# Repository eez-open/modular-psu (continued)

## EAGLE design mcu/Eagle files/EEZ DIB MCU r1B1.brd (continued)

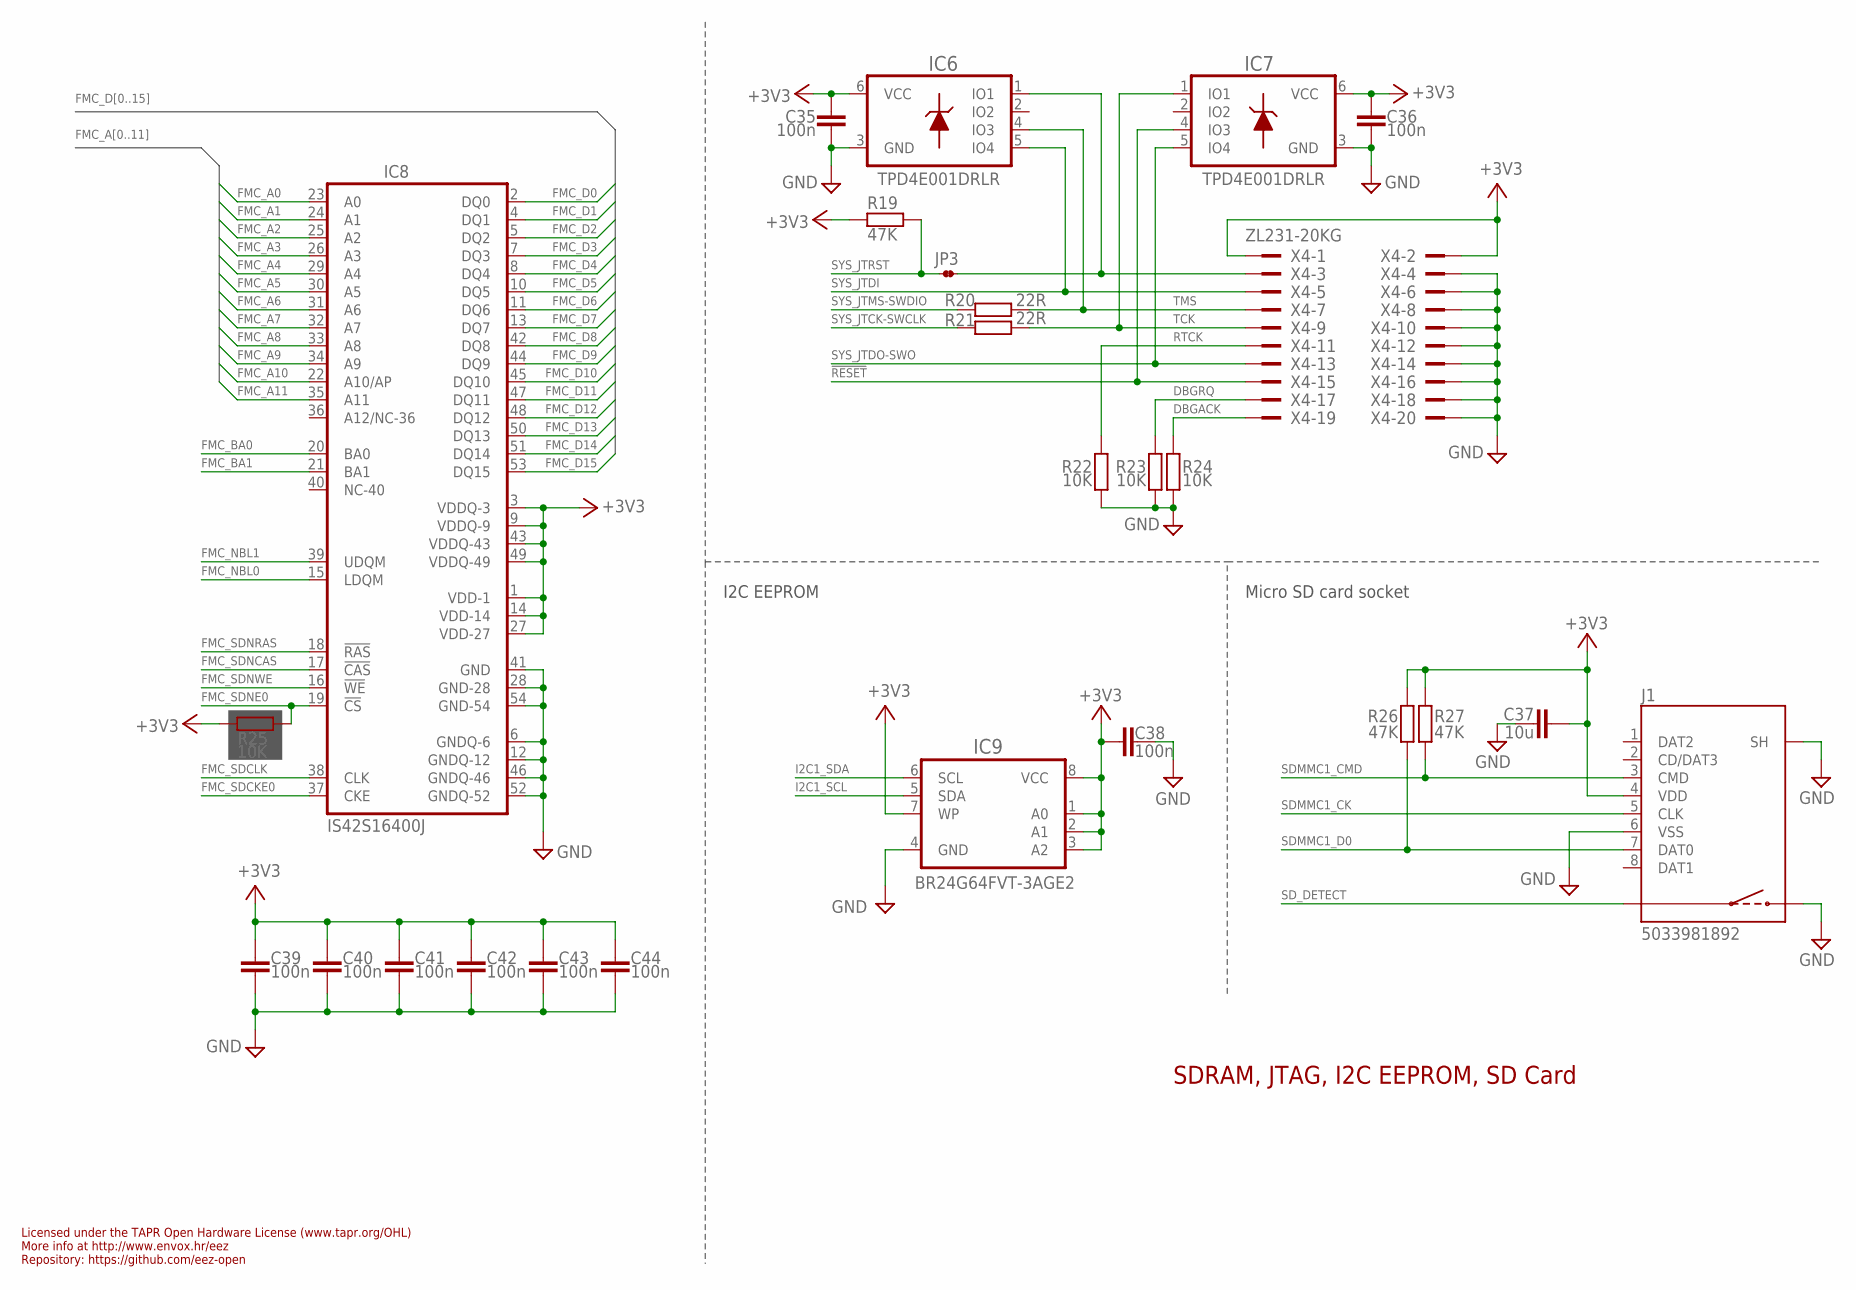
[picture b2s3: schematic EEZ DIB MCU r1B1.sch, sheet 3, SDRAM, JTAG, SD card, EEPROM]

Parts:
C35, C36, C38, C39, C40, C41, C42, C43, C44: 100n; C0603
C37: 10u; C1210
IC6, IC7: TPD4E001DRLR; DRL6
IC8: IS42S16400J; TSOPII-54
IC9: BR24G64FVT-3AGE2; PW8_TSSOP8
J1: 5033981892
JP3: JP2-NOCUT
R19, R26, R27: 47K; R0805
R20, R21: 22R; R0805
R22, R23, R24, R25: 10K; R0805
X4: ZL231-20KG; ML20L

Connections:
!RESET: IC7.4 (IO3), X4.15; also elsewhere on the board
+3V3: C35.1, C36.1, C37.1, C38.2, C39.1, C40.1, C41.1, C42.1, C43.1, C44.1, IC6.6 (VCC), IC7.6 (VCC), IC8.1 (VDD-1), IC8.3 (VDDQ-3), IC8.9 (VDDQ-9), IC8.14 (VDD-14), IC8.27 (VDD-27), IC8.43 (VDDQ-43), IC8.49 (VDDQ-49), IC9.1 (A0), IC9.2 (A1), IC9.3 (A2), IC9.7 (WP), IC9.8 (VCC), J1.4 (VDD), R19.1, R25.1, R26.1, R27.1, X4.1, X4.2; also elsewhere on the board
DBGACK: R24.1, X4.19
DBGRQ: R23.1, X4.17
FMC_A0: IC8.23 (A0); also elsewhere on the board
FMC_A1: IC8.24 (A1); also elsewhere on the board
FMC_A2: IC8.25 (A2); also elsewhere on the board
FMC_A3: IC8.26 (A3); also elsewhere on the board
FMC_A4: IC8.29 (A4); also elsewhere on the board
FMC_A5: IC8.30 (A5); also elsewhere on the board
FMC_A6: IC8.31 (A6); also elsewhere on the board
FMC_A7: IC8.32 (A7); also elsewhere on the board
FMC_A8: IC8.33 (A8); also elsewhere on the board
FMC_A9: IC8.34 (A9); also elsewhere on the board
FMC_A10: IC8.22 (A10/AP); also elsewhere on the board
FMC_A11: IC8.35 (A11); also elsewhere on the board
FMC_BA0: IC8.20 (BA0); also elsewhere on the board
FMC_BA1: IC8.21 (BA1); also elsewhere on the board
FMC_D0: IC8.2 (DQ0); also elsewhere on the board
FMC_D1: IC8.4 (DQ1); also elsewhere on the board
FMC_D2: IC8.5 (DQ2); also elsewhere on the board
FMC_D3: IC8.7 (DQ3); also elsewhere on the board
FMC_D4: IC8.8 (DQ4); also elsewhere on the board
FMC_D5: IC8.10 (DQ5); also elsewhere on the board
FMC_D6: IC8.11 (DQ6); also elsewhere on the board
FMC_D7: IC8.13 (DQ7); also elsewhere on the board
FMC_D8: IC8.42 (DQ8); also elsewhere on the board
FMC_D9: IC8.44 (DQ9); also elsewhere on the board
FMC_D10: IC8.45 (DQ10); also elsewhere on the board
FMC_D11: IC8.47 (DQ11); also elsewhere on the board
FMC_D12: IC8.48 (DQ12); also elsewhere on the board
FMC_D13: IC8.50 (DQ13); also elsewhere on the board
FMC_D14: IC8.51 (DQ14); also elsewhere on the board
FMC_D15: IC8.53 (DQ15); also elsewhere on the board
FMC_NBL0: IC8.15 (LDQM); also elsewhere on the board
FMC_NBL1: IC8.39 (UDQM); also elsewhere on the board
FMC_SDCKE0: IC8.37 (CKE); also elsewhere on the board
FMC_SDCLK: IC8.38 (CLK); also elsewhere on the board
FMC_SDNCAS: IC8.17 (!CAS); also elsewhere on the board
FMC_SDNE0: IC8.19 (!CS), R25.2; also elsewhere on the board
FMC_SDNRAS: IC8.18 (!RAS); also elsewhere on the board
FMC_SDNWE: IC8.16 (!WE); also elsewhere on the board
GND: C35.2, C36.2, C37.2, C38.1, C39.2, C40.2, C41.2, C42.2, C43.2, C44.2, IC6.3 (GND), IC7.3 (GND), IC8.6 (GNDQ-6), IC8.12 (GNDQ-12), IC8.28 (GND-28), IC8.41 (GND), IC8.46 (GNDQ-46), IC8.52 (GNDQ-52), IC8.54 (GND-54), IC9.4 (GND), J1.6 (VSS), J1.S (SH), J1.SW2, R22.2, R23.2, R24.2, X4.4, X4.6, X4.8, X4.10, X4.12, X4.14, X4.16, X4.18, X4.20; also elsewhere on the board
I2C1_SCL: IC9.5 (SDA); also elsewhere on the board
I2C1_SDA: IC9.6 (SCL); also elsewhere on the board
RTCK: R22.1, X4.11
SDMMC1_CK: J1.5 (CLK); also elsewhere on the board
SDMMC1_CMD: J1.3 (CMD), R27.2; also elsewhere on the board
SDMMC1_D0: J1.7 (DAT0), R26.2; also elsewhere on the board
SD_DETECT: J1.SW1; also elsewhere on the board
SYS_JTCK-SWCLK: R21.1; also elsewhere on the board
SYS_JTDI: IC6.5 (IO4), X4.5; also elsewhere on the board
SYS_JTDO-SWO: IC7.5 (IO4), X4.13; also elsewhere on the board
SYS_JTMS-SWDIO: R20.1; also elsewhere on the board
SYS_JTRST: JP3.1, R19.2; also elsewhere on the board
TCK: IC7.1 (IO1), R21.2, X4.9
TMS: IC6.4 (IO3), R20.2, X4.7
TRST: IC6.1 (IO1), JP3.2, X4.3

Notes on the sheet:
SDRAM, JTAG, I2C EEPROM, SD Card
Licensed under the TAPR Open Hardware License (www.tapr.org/OHL)
Repository: https://github.com/eez-open
More info at http://www.envox.hr/eez
I2C EEPROM
Micro SD card socket

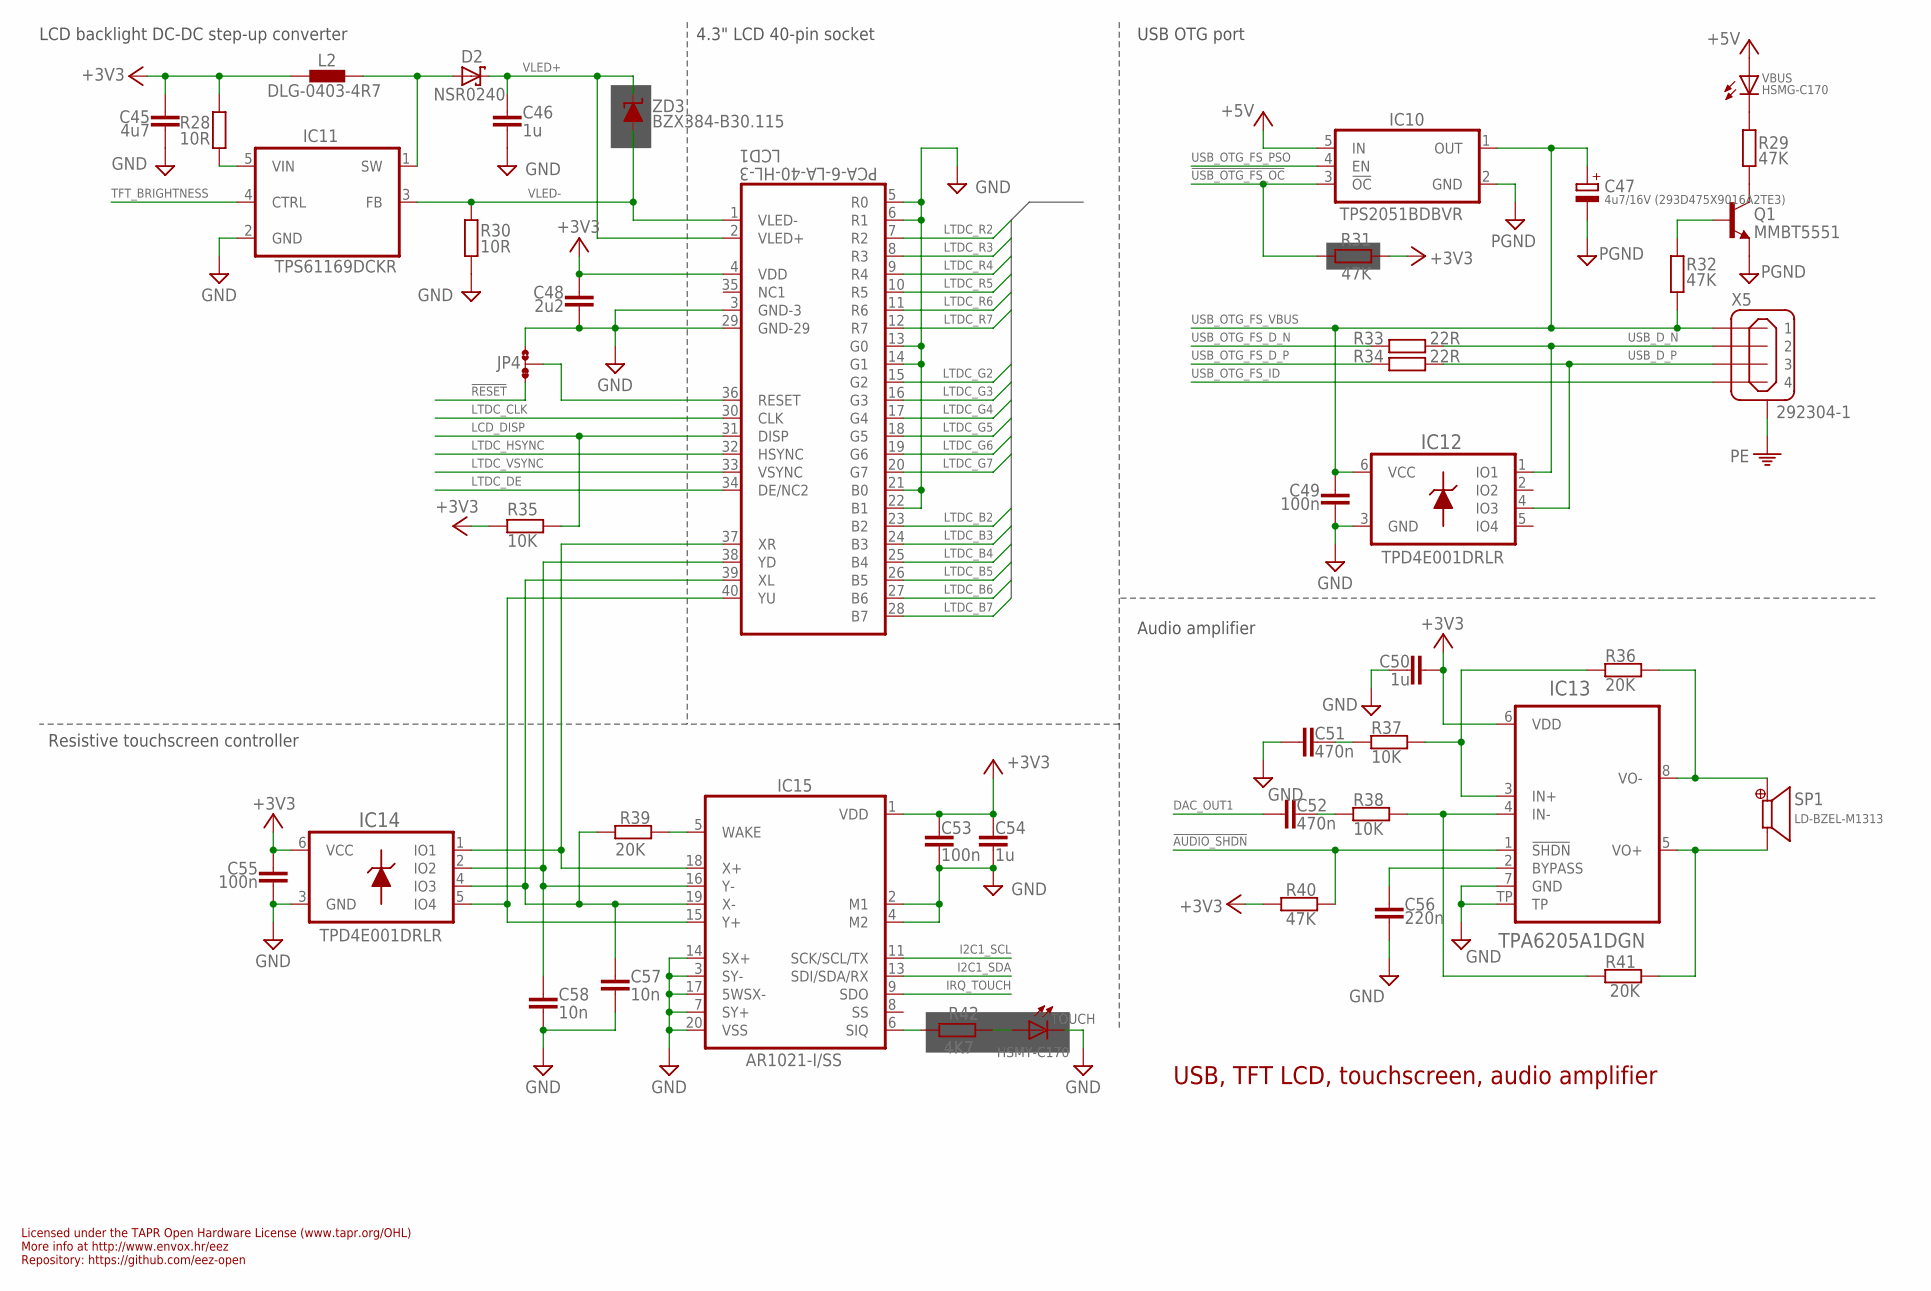
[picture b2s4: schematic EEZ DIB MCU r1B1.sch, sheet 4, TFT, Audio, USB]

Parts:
C45: 4u7; C1206
C46, C50, C54: 1u; C0805
C47: 4u7/16V (293D475X9016A2TE3); EC1206
C48: 2u2; C0805
C49, C53, C55: 100n; C0603
C51, C52: 470n; C0805
C56: 220n; C0805
C57, C58: 10n; C0805
D2: NSR0240; SOD123
IC10: TPS2051BDBVR; DBV5
IC11: TPS61169DCKR; DCK5
IC12, IC14: TPD4E001DRLR; DRL6
IC13: TPA6205A1DGN; SOP65P490X110-9N
IC15: AR1021-I/SS; SOP65P780X200-20N
JP4: JP3-CUT
L2: DLG-0403-4R7; DE0403
LCD1: PCA-6-LA-40-HL-3; FPC_40
Q1: MMBT5551; SOT23-BEC
R28, R30: 10R; R0805
R29, R31, R32, R40: 47K; R0805
R33, R34: 22R; R0805
R35, R37, R38: 10K; R0805
R36, R39, R41: 20K; R0805
R42: 4K7; R0805
SP1: LD-BZEL-M1313
TOUCH: HSMY-C170; LED_0805
VBUS: HSMG-C170; LED_0805
X5: 292304-1; USB-B
ZD3: BZX384-B30.115; SOD323-W

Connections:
!AUDIO_SHDN: IC13.1 (!SHDN), R40.1
!RESET: JP4.NC; also elsewhere on the board
!USB_OTG_FS_OC: IC10.3 (!OC), R31.1; also elsewhere on the board
+3V3: C45.1, C48.1, C50.2, C53.2, C54.2, C55.2, IC13.6 (VDD), IC14.6 (VCC), IC15.1 (VDD), L2.1, LCD1.4 (VDD), R28.1, R31.2, R35.2, R40.2; also elsewhere on the board
+5V: IC10.5 (IN), VBUS.A; also elsewhere on the board
DAC_OUT1: C52.2; also elsewhere on the board
GND: C45.2, C46.2, C47.-, C48.2, C49.1, C50.1, C51.2, C53.1, C54.1, C55.1, C56.1, C57.2, C58.2, IC10.2 (GND), IC11.2 (GND), IC12.3 (GND), IC13.7 (GND), IC13.TP, IC14.3 (GND), IC15.2 (M1), IC15.3 (SY-), IC15.4 (M2), IC15.7 (SY+), IC15.14 (SX+), IC15.17 (5WSX-), IC15.20 (VSS), JP4.NO, LCD1.3 (GND-3), LCD1.5 (R0), LCD1.6 (R1), LCD1.13 (G0), LCD1.14 (G1), LCD1.21 (B0), LCD1.22 (B1), LCD1.29 (GND-29), Q1.E, R30.2, TOUCH.C; also elsewhere on the board
I2C1_SCL: IC15.11 (SCK/SCL/TX); also elsewhere on the board
I2C1_SDA: IC15.13 (SDI/SDA/RX); also elsewhere on the board
IRQ_TOUCH: IC15.9 (SDO); also elsewhere on the board
LCD_DISP: LCD1.31 (DISP), R35.1
LTDC_B2: LCD1.23 (B2); also elsewhere on the board
LTDC_B3: LCD1.24 (B3); also elsewhere on the board
LTDC_B4: LCD1.25 (B4); also elsewhere on the board
LTDC_B5: LCD1.26 (B5); also elsewhere on the board
LTDC_B6: LCD1.27 (B6); also elsewhere on the board
LTDC_B7: LCD1.28 (B7); also elsewhere on the board
LTDC_CLK: LCD1.30 (CLK); also elsewhere on the board
LTDC_DE: LCD1.34 (DE/NC2); also elsewhere on the board
LTDC_G2: LCD1.15 (G2); also elsewhere on the board
LTDC_G3: LCD1.16 (G3); also elsewhere on the board
LTDC_G4: LCD1.17 (G4); also elsewhere on the board
LTDC_G5: LCD1.18 (G5); also elsewhere on the board
LTDC_G6: LCD1.19 (G6); also elsewhere on the board
LTDC_G7: LCD1.20 (G7); also elsewhere on the board
LTDC_HSYNC: LCD1.32 (HSYNC); also elsewhere on the board
LTDC_R2: LCD1.7 (R2); also elsewhere on the board
LTDC_R3: LCD1.8 (R3); also elsewhere on the board
LTDC_R4: LCD1.9 (R4); also elsewhere on the board
LTDC_R5: LCD1.10 (R5); also elsewhere on the board
LTDC_R6: LCD1.11 (R6); also elsewhere on the board
LTDC_R7: LCD1.12 (R7); also elsewhere on the board
LTDC_VSYNC: LCD1.33 (VSYNC); also elsewhere on the board
unnamed: R29.2, VBUS.C
unnamed: C57.1, IC14.4 (IO3), IC15.19 (X-), LCD1.39 (XL), R39.2
unnamed: IC14.1 (IO1), IC15.18 (X+), LCD1.37 (XR)
unnamed: IC15.5 (WAKE), R39.1
unnamed: C58.1, IC14.2 (IO2), IC15.16 (Y-), LCD1.38 (YD)
unnamed: R42.1, TOUCH.A
unnamed: IC15.6 (SIQ), R42.2
unnamed: Q1.C, R29.1
unnamed: Q1.B, R32.2
unnamed: JP4.COM, LCD1.36 (RESET)
unnamed: IC11.5 (VIN), R28.2
unnamed: IC13.5 (VO+), R41.1, SP1.-
unnamed: IC14.5 (IO4), IC15.15 (Y+), LCD1.40 (YU)
unnamed: IC13.8 (VO-), R36.1, SP1.+
unnamed: IC13.4 (IN-), R38.1, R41.2
unnamed: IC13.3 (IN+), R36.2, R37.1
unnamed: C51.1, R37.2
unnamed: C56.2, IC13.2 (BYPASS)
unnamed: C52.1, R38.2
PE: X5.M1 (SHIELD), X5.M2 (SHIELD); also elsewhere on the board
SW_WLED: D2.A, IC11.1 (SW), L2.2
TFT_BRIGHTNESS: IC11.4 (CTRL); also elsewhere on the board
USB_D_N: IC12.1 (IO1), R33.1, X5.2
USB_D_P: IC12.4 (IO3), R34.1, X5.3
USB_OTG_FS_D_N: R33.2; also elsewhere on the board
USB_OTG_FS_D_P: R34.2; also elsewhere on the board
USB_OTG_FS_ID: X5.4; also elsewhere on the board
USB_OTG_FS_PSO: IC10.4 (EN); also elsewhere on the board
USB_OTG_FS_VBUS: C47.+, C49.2, IC10.1 (OUT), IC12.6 (VCC), R32.1, X5.1; also elsewhere on the board
VLED+: C46.1, D2.C, LCD1.2 (VLED+), ZD3.C
VLED-: IC11.3 (FB), LCD1.1 (VLED-), R30.1, ZD3.A

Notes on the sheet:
USB, TFT LCD, touchscreen, audio amplifier
Licensed under the TAPR Open Hardware License (www.tapr.org/OHL)
Repository: https://github.com/eez-open
More info at http://www.envox.hr/eez
4.3" LCD 40-pin socket
LCD backlight DC-DC step-up converter
USB OTG port
Resistive touchscreen controller
Audio amplifier

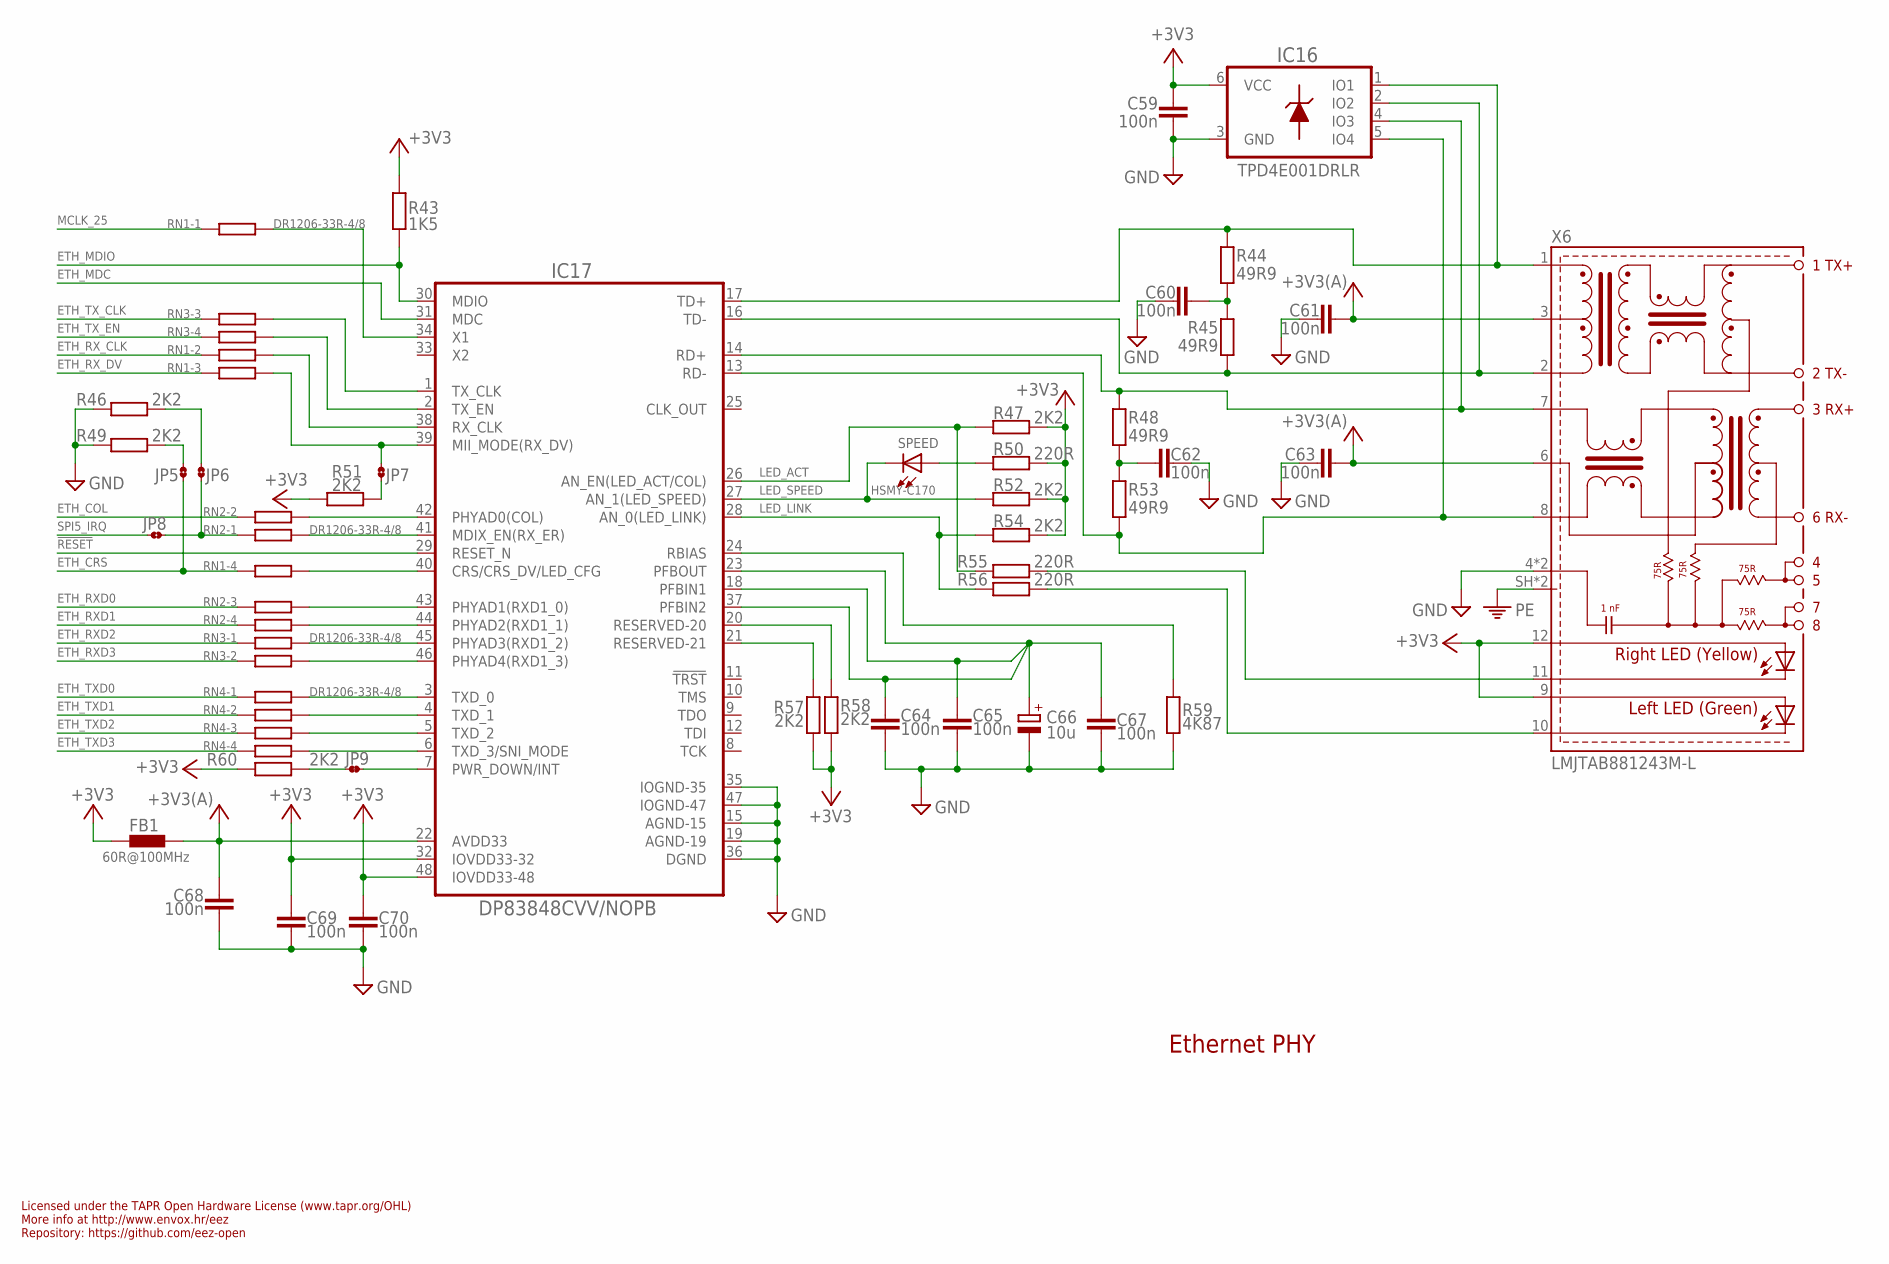
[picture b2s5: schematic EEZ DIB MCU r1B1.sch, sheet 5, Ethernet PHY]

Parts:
C59, C60, C61, C62, C63, C64, C65, C67, C68, C69, C70: 100n; C0603
C66: 10u; EC1206
FB1: 60R@100MHz; BEAD0603
IC16: TPD4E001DRLR; DRL6
IC17: DP83848CVV/NOPB; PT48
JP5, JP6, JP7, JP8: JP2-CUT
JP9: JP2-NOCUT
R43: 1K5; R0805
R44, R45, R48, R53: 49R9; R0805
R46, R47, R49, R51, R52, R54, R57, R58, R60: 2K2; R0805
R50, R55, R56: 220R; R0805
R59: 4K87; R0603
RN1, RN2, RN3, RN4: DR1206-33R-4/8; CAY16
SPEED: HSMY-C170; LED_0805
X6: LMJTAB881243M-L; RJ45-TRAFO-LED

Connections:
!RESET: IC17.29 (RESET_N); also elsewhere on the board
+3V3: C59.1, C69.1, C70.1, FB1.P$1 (1), IC16.6 (VCC), IC17.32 (IOVDD33-32), IC17.48 (IOVDD33-48), R43.2, R47.1, R50.1, R51.1, R52.1, R54.1, R57.1, R58.1, R60.1, X6.9 (GREEN-A), X6.12 (YELLOW_A); also elsewhere on the board
+3V3(A): C61.2, C63.2, C68.1, FB1.P$2 (2), IC17.22 (AVDD33), X6.3 (CT), X6.6 (CR)
ETH_COL: RN2.2 (1); also elsewhere on the board
ETH_CRS: JP5.1, RN1.4 (1); also elsewhere on the board
ETH_MDC: IC17.31 (MDC); also elsewhere on the board
ETH_MDIO: IC17.30 (MDIO), R43.1; also elsewhere on the board
ETH_RXD0: RN2.3 (1); also elsewhere on the board
ETH_RXD1: RN2.4 (1); also elsewhere on the board
ETH_RXD2: RN3.1; also elsewhere on the board
ETH_RXD3: RN3.2 (1); also elsewhere on the board
ETH_RX_CLK: RN1.2 (1); also elsewhere on the board
ETH_RX_DV: RN1.3 (1); also elsewhere on the board
ETH_RX_ER: JP6.1, JP8.1, RN2.1
ETH_TXD0: RN4.1; also elsewhere on the board
ETH_TXD1: RN4.2 (1); also elsewhere on the board
ETH_TXD2: RN4.3 (1); also elsewhere on the board
ETH_TXD3: RN4.4 (1); also elsewhere on the board
ETH_TX_CLK: RN3.3 (1); also elsewhere on the board
ETH_TX_EN: RN3.4 (1); also elsewhere on the board
GND: C59.2, C60.2, C61.1, C62.2, C63.1, C64.2, C65.2, C66.-, C67.2, C68.2, C69.2, C70.2, IC16.3 (GND), IC17.15 (AGND-15), IC17.19 (AGND-19), IC17.35 (IOGND-35), IC17.36 (DGND), IC17.47 (IOGND-47), R46.1, R49.1, R59.1, X6.4 (GND), X6.5 (GND); also elsewhere on the board
LED_ACT: IC17.26 (AN_EN(LED_ACT/COL)), R47.2, R55.2
LED_LINK: IC17.28 (AN_0(LED_LINK)), R54.2, R56.2
LED_SPEED: IC17.27 (AN_1(LED_SPEED)), R52.2, SPEED.C
MCLK_25: RN1.1; also elsewhere on the board
unnamed: IC17.1 (TX_CLK), RN3.6 (2)
unnamed: C60.1, R44.1, R45.2
unnamed: R55.1, X6.11 (YELLOW-C)
unnamed: R56.1, X6.10 (GREEN-C)
unnamed: IC17.2 (TX_EN), RN3.5 (2)
unnamed: IC17.39 (MII_MODE(RX_DV)), JP7.2, RN1.6 (2)
unnamed: IC17.38 (RX_CLK), RN1.7 (2)
unnamed: IC17.3 (TXD_0), RN4.8 (2)
unnamed: IC17.4 (TXD_1), RN4.7 (2)
unnamed: IC17.5 (TXD_2), RN4.6 (2)
unnamed: IC17.34 (X1), RN1.8 (2)
unnamed: JP7.1, R51.2
unnamed: JP5.2, R49.2
unnamed: JP6.2, R46.2
unnamed: IC17.7 (PWR_DOWN/INT), JP9.2
unnamed: JP9.1, R60.2
unnamed: IC17.6 (TXD_3/SNI_MODE), RN4.5 (2)
unnamed: IC17.46 (PHYAD4(RXD1_3)), RN3.7 (2)
unnamed: IC17.45 (PHYAD3(RXD1_2)), RN3.8 (2)
unnamed: IC17.42 (PHYAD0(COL)), RN2.7 (2)
unnamed: IC17.44 (PHYAD2(RXD1_1)), RN2.5 (2)
unnamed: IC17.43 (PHYAD1(RXD1_0)), RN2.6 (2)
unnamed: IC17.41 (MDIX_EN(RX_ER)), RN2.8 (2)
unnamed: IC17.40 (CRS/CRS_DV/LED_CFG), RN1.5 (2)
unnamed: IC17.24 (RBIAS), R59.2
unnamed: IC17.21 (RESERVED-21), R57.2
unnamed: IC17.20 (RESERVED-20), R58.2
unnamed: R50.2, SPEED.A
unnamed: C62.1, R48.1, R53.2
PE: X6.SH, X6.SH2 (SH); also elsewhere on the board
PFBOUT: C64.1, C65.1, C66.+, C67.1, IC17.18 (PFBIN1), IC17.23 (PFBOUT), IC17.37 (PFBIN2)
RD+: IC16.4 (IO3), IC17.14 (RD+), R48.2, X6.7 (RD+)
RD-: IC16.5 (IO4), IC17.13 (RD-), R53.1, X6.8 (RD-)
SPI5_IRQ: JP8.2; also elsewhere on the board
TD+: IC16.1 (IO1), IC17.17 (TD+), R44.2, X6.1 (TD+)
TD-: IC16.2 (IO2), IC17.16 (TD-), R45.1, X6.2 (TD-)

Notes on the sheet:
Ethernet PHY
Licensed under the TAPR Open Hardware License (www.tapr.org/OHL)
Repository: https://github.com/eez-open
More info at http://www.envox.hr/eez

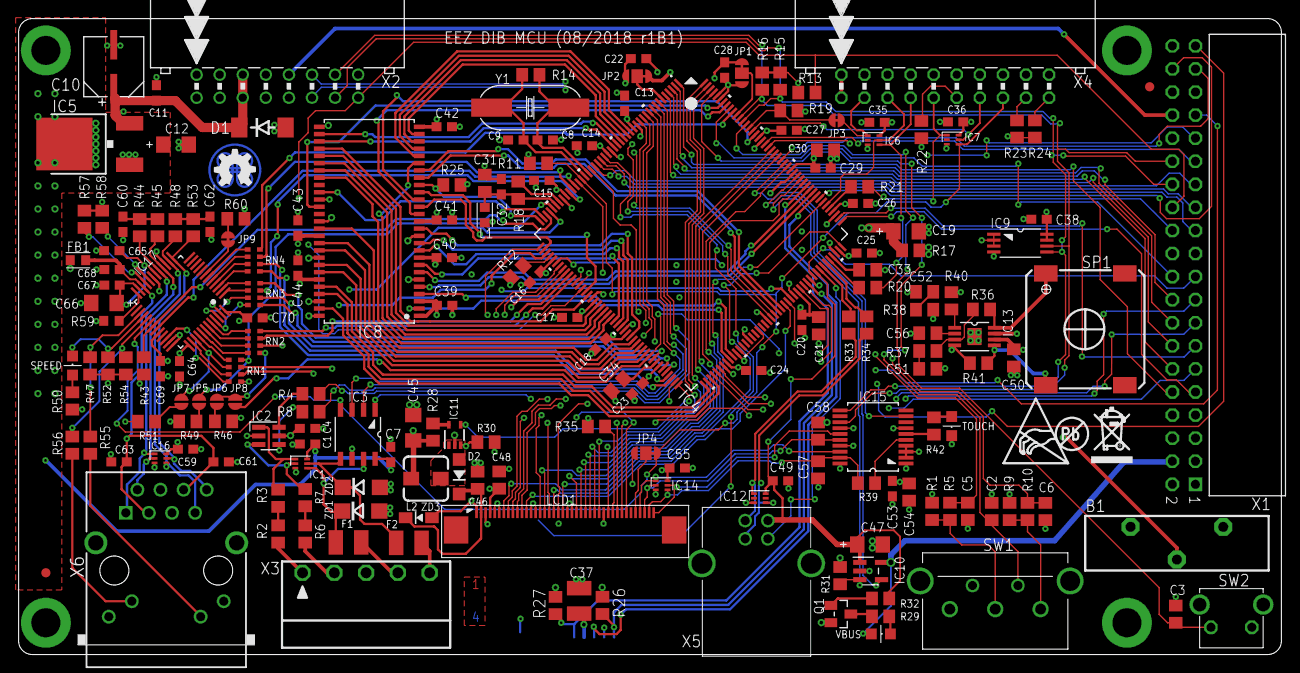
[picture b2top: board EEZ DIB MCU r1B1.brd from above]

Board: 4 copper layers, 139.0 x 70.0 mm, 193 parts (1 on the bottom side), 233 nets.

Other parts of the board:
EEZ_SIGNATURE: SIGNATURESMALL; SIGNATURE_5MM
U$1: RECYCLE_BIN1/8
U$5: PB_SMALL
U$6: ESD_SYMBOL

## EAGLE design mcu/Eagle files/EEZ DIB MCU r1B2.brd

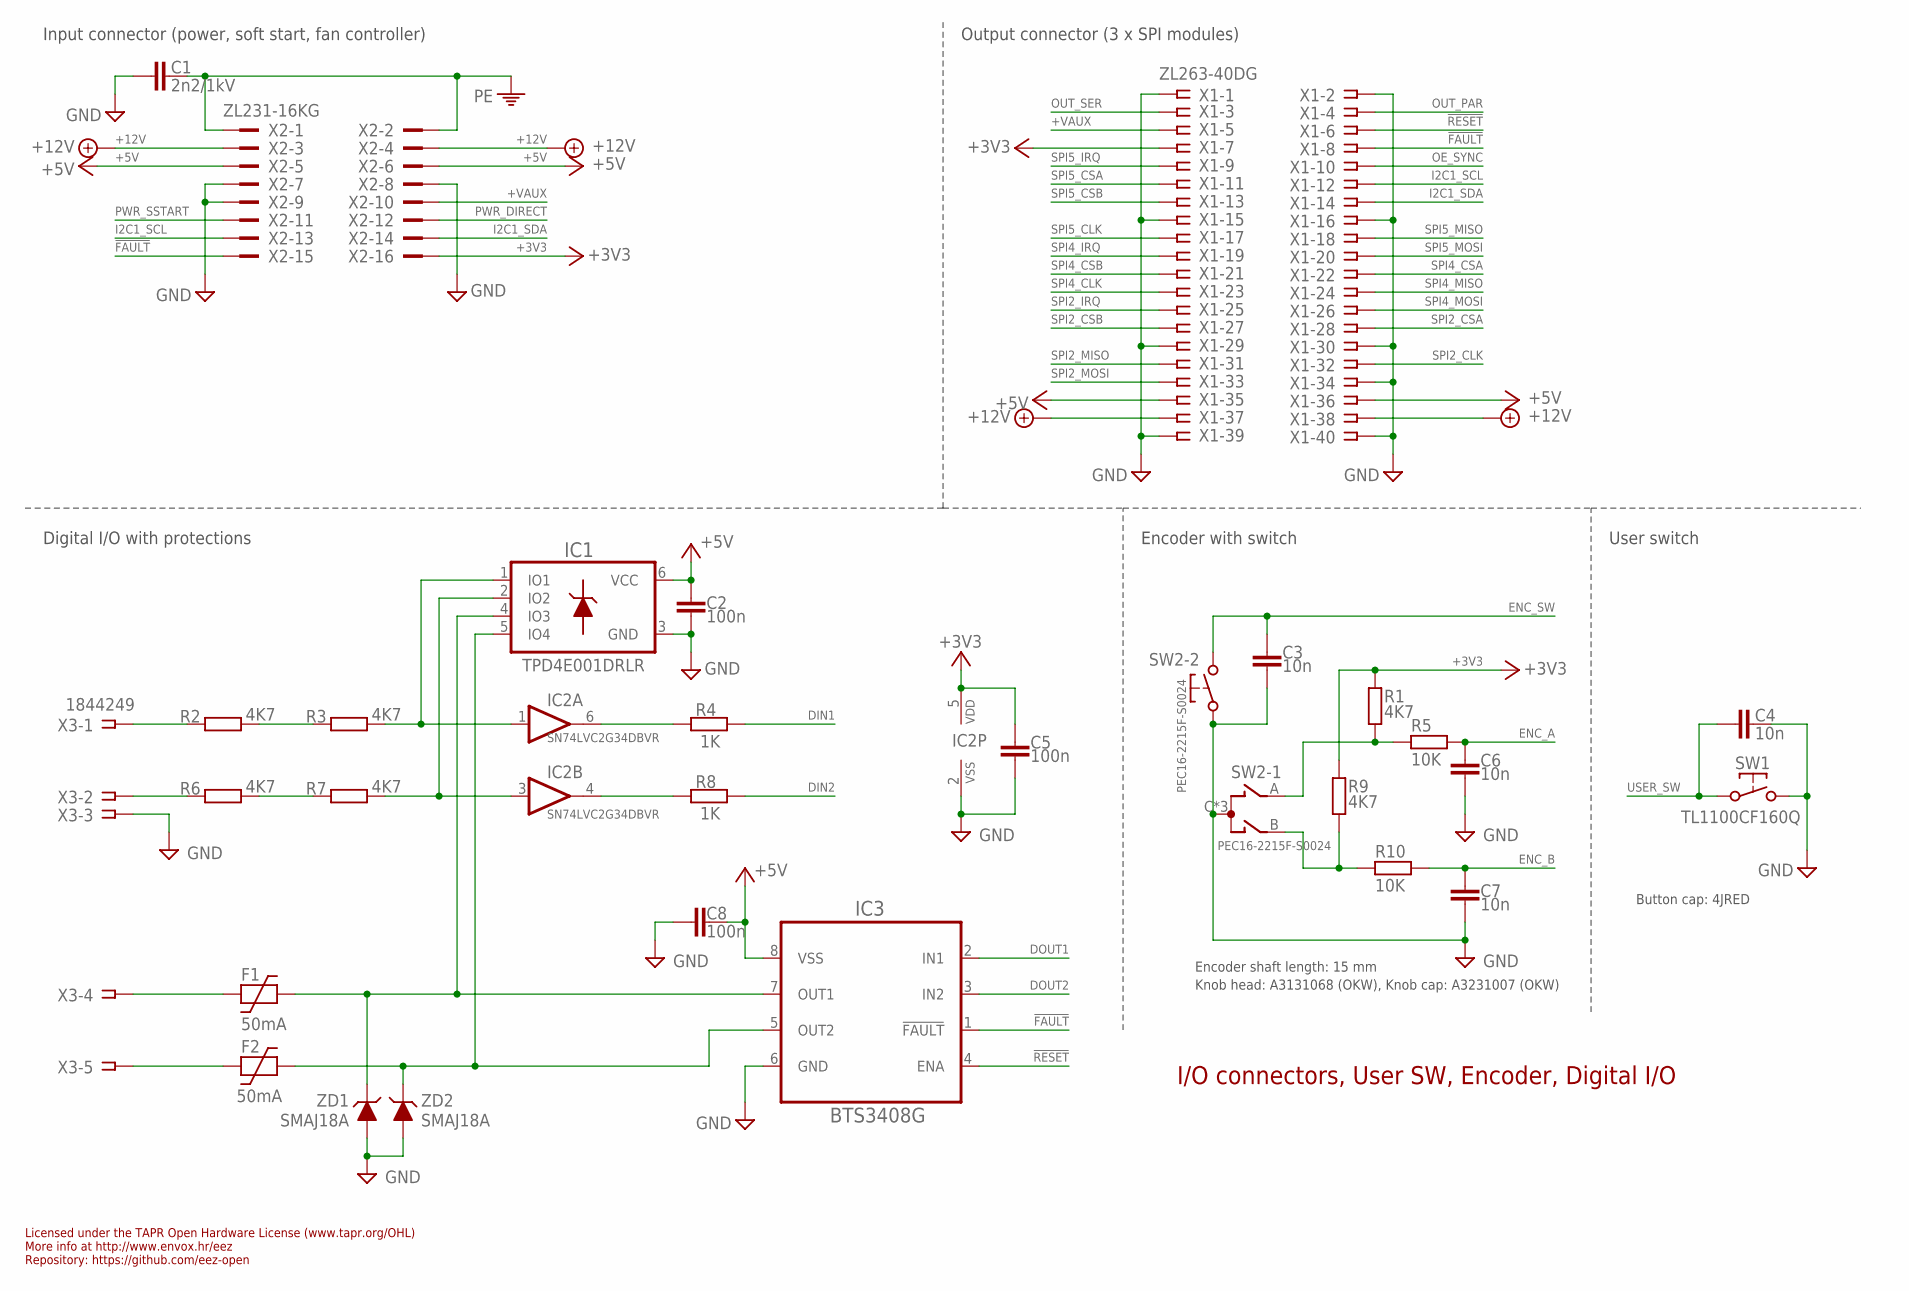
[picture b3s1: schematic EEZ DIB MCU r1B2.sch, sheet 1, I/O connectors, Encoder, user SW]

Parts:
C1: 2n2/1kV; C1210
C2, C5, C8: 100n; C0603
C3, C4, C6, C7: 10n; C0805
F1, F2: 50mA; F1210
IC1: TPD4E001DRLR; DRL6
IC2: SN74LVC2G34DBVR; DBV6
IC3: BTS3408G; SOIC127P600X173-8N
R1, R2, R3, R6, R7, R9: 4K7; R0805
R4, R8: 1K; R0805
R5, R10: 10K; R0805
SW1: TL1100CF160Q; TL1100C
SW2: PEC16-2215F-S0024; PEC16-2215F
X1: ZL263-40DG
X2: ZL231-16KG; ML16L
X3: 1844249; MC1,5/5-G-3,5
ZD1, ZD2: SMAJ18A; DO214AC

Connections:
!FAULT: IC3.1 (!FAULT), X1.8, X2.15; also elsewhere on the board
!RESET: IC3.4 (ENA), X1.6; also elsewhere on the board
+3V3: C5.1, IC2.5 (VDD), R1.1, R9.1, X1.7, X2.16; also elsewhere on the board
+5V: C2.1, C8.2, IC1.6 (VCC), IC3.8 (VSS), X1.35, X1.36, X2.5, X2.6; also elsewhere on the board
+12V: X1.37, X1.38, X2.3, X2.4
+VAUX: X1.5, X2.10
DIN1: R4.2; also elsewhere on the board
DIN2: R8.2; also elsewhere on the board
DOUT1: IC3.2 (IN1); also elsewhere on the board
DOUT2: IC3.3 (IN2); also elsewhere on the board
ENC_A: C6.2, R5.1; also elsewhere on the board
ENC_B: C7.1, R10.1; also elsewhere on the board
ENC_SW: C3.2, SW2.E (2); also elsewhere on the board
EOUT_A: R9.2, R10.2, SW2.B
EOUT_B: R1.2, R5.2, SW2.A
GND: C1.2, C2.2, C3.1, C4.1, C5.2, C6.1, C7.2, C8.1, IC1.3 (GND), IC2.2 (VSS), IC3.6 (GND), SW1.2, SW2.C, SW2.D (1), SW2.GND1 (C), SW2.GND2 (C), X1.1, X1.2, X1.15, X1.16, X1.29, X1.30, X1.34, X1.39, X1.40, X2.7, X2.8, X2.9, X3.3, ZD1.A, ZD2.A; also elsewhere on the board
I2C1_SCL: X1.12, X2.13; also elsewhere on the board
I2C1_SDA: X1.14, X2.14; also elsewhere on the board
unnamed: R2.2, R3.1
unnamed: R2.1, X3.1
unnamed: R6.1, X3.2
unnamed: R6.2, R7.1
unnamed: IC2.6 (O), R4.1
unnamed: IC2.4 (O), R8.1
unnamed: F1.1, X3.4
unnamed: F2.1, X3.5
unnamed: IC1.1 (IO1), IC2.1 (I), R3.2
unnamed: IC1.2 (IO2), IC2.3 (I), R7.2
unnamed: F1.2, IC1.4 (IO3), IC3.7 (OUT1), ZD1.C
unnamed: F2.2, IC1.5 (IO4), IC3.5 (OUT2), ZD2.C
OE_SYNC: X1.10; also elsewhere on the board
OUT_PAR: X1.4; also elsewhere on the board
OUT_SER: X1.3; also elsewhere on the board
PE: C1.1, X2.1, X2.2; also elsewhere on the board
PWR_DIRECT: X2.12; also elsewhere on the board
PWR_SSTART: X2.11; also elsewhere on the board
SPI2_CLK: X1.32; also elsewhere on the board
SPI2_CSA: X1.28; also elsewhere on the board
SPI2_CSB: X1.27; also elsewhere on the board
SPI2_IRQ: X1.25; also elsewhere on the board
SPI2_MISO: X1.31; also elsewhere on the board
SPI2_MOSI: X1.33; also elsewhere on the board
SPI4_CLK: X1.23; also elsewhere on the board
SPI4_CSA: X1.22; also elsewhere on the board
SPI4_CSB: X1.21; also elsewhere on the board
SPI4_IRQ: X1.19; also elsewhere on the board
SPI4_MISO: X1.24; also elsewhere on the board
SPI4_MOSI: X1.26; also elsewhere on the board
SPI5_CLK: X1.17; also elsewhere on the board
SPI5_CSA: X1.11; also elsewhere on the board
SPI5_CSB: X1.13; also elsewhere on the board
SPI5_IRQ: X1.9; also elsewhere on the board
SPI5_MISO: X1.18; also elsewhere on the board
SPI5_MOSI: X1.20; also elsewhere on the board
USER_SW: C4.2, SW1.1; also elsewhere on the board

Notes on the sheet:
Licensed under the TAPR Open Hardware License (www.tapr.org/OHL)
Repository: https://github.com/eez-open
More info at http://www.envox.hr/eez
Encoder shaft length: 15 mm
Knob head: A3131068 (OKW), Knob cap: A3231007 (OKW)
I/O connectors, User SW, Encoder, Digital I/O
Digital I/O with protections
Encoder with switch
User switch
Input connector (power, soft start, fan controller)
Output connector (3 x SPI modules)
Button cap: 4JRED
